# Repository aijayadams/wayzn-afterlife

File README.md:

# wayzn-afterlife

**Your Wayzn dog door doesn't have to die with the cloud, and it can come back better.**

Wayzn is shutting its service down in March 2027. The door on your slider is still a
good machine: a strong motor, a careful motor controller and a thermal sensor that sees
your dog. Only its "brain" was tied to the cloud. Swap that brain for a small ESP32
board and the door keeps working, entirely on your own network.

![Three stages. Original: the Wayzn app, Wayzn's cloud and the Electric Imp cloud drive the imp module, which drives Wayzn's STM32 motor controller and DRV8828 motor driver. Phase A, working today: your home automation talks over local Wi-Fi to an ESP32 brain that replaces the imp; Wayzn's STM32 and driver stay. Phase B, in design: one ESP32-C5 on our own board does the brain and the motor control, with a DRV8876 driver; the STM32 is gone. The door's motor, encoder, thermal sensor and case are kept throughout.](docs/before-after.svg)

## Two phases

| | What it is | Status |
|---|---|---|
| **[Phase A](#phase-a-an-esp32-brain-on-your-existing-board)** | Add an ESP32 dev board to the door's existing control board. It takes over from the cloud brain and controls the original hardware. | **Works today.** Running in a real door every day. |
| **[Phase B](#phase-b-a-replacement-control-board-in-design)** | A new control board that replaces Wayzn's entirely: same size, same connectors, an ESP32 that drives the motor itself. | **In design and validation.** Not ready to build yet. |

If you have a Wayzn door and want it working after the shutdown, **Phase A is the one to
do.**

## Phase A: an ESP32 brain on your existing board

### What you get

- **A door that keeps working.** No account, no cloud, no company that can switch it
  off.
- **Local control.** A small HTTP API on your network: open, close, live status (open,
  closed, opening, closing) and the door's settings, such as auto-open, how far it
  opens, how long it holds and how sensitive it is. A Home Assistant integration that
  uses it is available (pictured below).
- **Smarter dog detection.** The brain sees every raw reading from the door's thermal
  sensor, so it can do much better than a grid of cells and a small/medium/large
  setting. Fewer false opens, and a door that doesn't close on a dog standing beside it.
- **Safety first.** The original motor-control and current-limit (strength) firmware
  keeps running, untouched, so the door only ever pushes as hard as Wayzn designed it
  to. The door never closes on something it can see, and anything unexpected leaves it
  **open**: a dog is never locked out.
- **All open.** Firmware, wiring, measurements and the door's protocol are documented
  here, so you can fix and improve your own door.

### How it sees your dog

A tiny 8×8 thermal camera watches the doorway ten times a second. The brain keeps two
judgements apart: **presence** (a dog wants out, so open) and **occupied** (something is
in the doorway, so never close, and reverse if closing). Occupied is deliberately the
more sensitive one: a false alarm only keeps the door open a little longer. A new
detector that learns each pixel's own noise is already running alongside the current one
and catches dogs at the edge of the view that the original approach misses
([the numbers](docs/DETECTION-RESEARCH.md)).

### What it takes

If you're comfortable soldering a few wires to small pads, this is an evening's project.

1. **Open the door's case.** The shell is friction fit: no tools needed.
2. **Add an ESP32 and eight connections.** Seven wires and one jumper, all to test
   points and pads that Wayzn conveniently left on the board:

3. **Flash the firmware.** It's in [firmware/brain](firmware/brain/) (PlatformIO);
   updates after that go over Wi-Fi. The door then answers on its
   [local API](docs/API.md). For Home Assistant, the `wayzn` integration's local mode
   ([aijayadams/wayzn](https://github.com/aijayadams/wayzn)) talks to it.

## Phase B: a replacement control board (in design)

Phase A keeps Wayzn's original board and its motor controller. Phase B replaces that
board outright with an open design, so a door can be repaired or rebuilt without any
Wayzn parts, and so the motor control is open too.

#### The architecture

Wayzn's board splits the work between two chips: a cloud-connected Electric Imp module
makes the decisions, and an STM32 microcontroller runs the motor. Phase A swaps out
only the decision-maker. Phase B collapses everything into one ESP32 that both decides
and drives:

```mermaid
flowchart LR
  subgraph W["Wayzn's board (Phase A keeps it)"]
    direction TB
    IMP["Electric Imp<br/>cloud brain<br/>(Phase A: our ESP32)"] -- serial --> STM["STM32<br/>motor controller"]
    STM --> DRV1["DRV8828<br/>motor driver"]
  end
  subgraph B["Phase B board"]
    direction TB
    C5["ESP32-C5<br/>brain + motor control"] --> DRV2["DRV8876<br/>motor driver"]
    C5 -.- H2["ESP32-H2<br/>Thread, later"]
  end
```

- **One chip decides and drives.** The ESP32-C5 runs the door logic, the Wi-Fi API and
  the motor control loop. There is no second microcontroller and no serial link to keep
  in sync, and every part of the motor control is open code.
- **Hardware does the time-critical work.** The C5's built-in peripherals count every
  encoder pulse, generate the motor PWM, sample the motor current and react to a driver
  fault, all without the CPU. So Wi-Fi traffic can't make the motor miss a beat. The
  software only runs a slow outer loop: Wayzn's own controller ran at 10 ms.
- **Safety sits in silicon, not in code.** The motor driver caps the force on its own,
  at 1.1 A, matching Wayzn's limit. The motor's enable lines are held off by
  resistors, so a reset, crash or firmware update leaves the motor stopped. On top of
  that the firmware adds obstruction detection: it learns what a normal move draws and
  reverses toward open on anything more.
- **A drop-in fit.** The same outline, post holes and connector positions as Wayzn's
  board, measured from scans, so the door's cables, the case and the button cap fit
  unchanged. Below, the new board's parts are drawn over a scan of Wayzn's board: the
  red circles are the case's posts and the connector and button pins, all landing on
  Wayzn's own holes.

- **Room to grow.** An ESP32-H2 sits beside the C5 for Thread/Matter later, and an RGB
  LED under the door's light pipe gives the status more than one colour.

**Status:** the board is designed and has had an independent design review, and the
first prototypes are being ordered. It **hasn't been built or tested yet**, and the
firmware that drives the motor directly hasn't been written. Unless you want to help
validate it, use Phase A for now. Design notes: [docs/CONTROL-BOARD.md](docs/CONTROL-BOARD.md);
the KiCad project: [hardware/control-board](hardware/control-board/).

## Go deeper

| | |
|---|---|
| [How it works](docs/HOW-IT-WORKS.md) | Phase A: the board, its buses, what the motor controller does on its own, and how the brain is built |
| [Wiring](docs/HOW-IT-WORKS.md#wiring-the-esp32) | Phase A: the connection table behind the diagram above |
| [API](docs/API.md) | The brain's local HTTP API and every setting |
| [Detection research](docs/DETECTION-RESEARCH.md) | Thermal sensor measurements and the detector comparison |
| [Lab log](docs/LOG.md) · [plan](docs/PLAN.md) · [probing](docs/PROBING.md) | The research notebook: every session, the original plan and its decisions, and the probing procedures |
| [Original detection study](docs/research/2026-11-21-detection-study.md) · [captures](captures/) | The full Grid-EYE study with figures, and the raw UART/I2C logs the docs cite |
| [STM32 firmware](docs/STM-FIRMWARE.md) · [protocol](docs/STM-PROTOCOL.md) | Wayzn's motor controller: commands, states, status lines, and the motor driver's scales |
| [Hardware](docs/hardware/) | The Wayzn main board, its measured geometry, the STM32 pin map and the sensor board |
| [Control board](docs/CONTROL-BOARD.md) | Phase B: the replacement board's design, safety and control approach |
| [AGENTS.md](AGENTS.md) | The principles every change follows |

Wayzn's own STM32 firmware isn't published here; [tools/swd-dump](tools/swd-dump/) reads
your board's copy if you want one.

## What's where

| Path | Phase | What |
|---|---|---|
| `firmware/brain/` | A | The ESP32 brain firmware (PlatformIO) |
| `tools/` | A | The probing tools used to understand the board (UART/I2C sniffers, SWD dump, power test, Ghidra scripts) |
| `docs/` | A, B | How it works, the API, the door's protocol, measurements, and the Phase B design notes |
| `hardware/control-board/` | B | The replacement control board: KiCad project generated from Python, fab and order files |
| `hardware/carrier/` | A (parked) | A plug-in carrier PCB for the Phase A brain. Not needed (the dev-board wiring works); kept for reference |
| `photos/` | | Board photos and scans (serial labels blurred, no location data) |

## Join in

Own a Wayzn door? [Open an issue](https://github.com/aijayadams/wayzn-afterlife/issues)
with questions, your board's revision, photos, or ideas. Every door that keeps running
is a win.

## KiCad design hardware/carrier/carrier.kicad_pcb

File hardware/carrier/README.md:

# Phase A carrier board v3 (WYP-BC-100 piggyback, parked)

A 4-layer board (53.8 x 33.4 mm) that replaces the hand-wired ESP32 DevKit. It sits parallel to the Wayzn
WYP-BC-100, above the STM32 end, inside one ~57 mm cell between the lid ribs. It plugs in: no screws, no
spacers, no soldering to test points.

Status: **laid out by hand and checked (ERC, DRC with schematic parity, courtyards, silkscreen: all clean); not
ordered.** The Wayzn-side positions come from the photos plus caliper readings, so check the 1:1 print before
ordering (see "Before ordering").

Pictures: `out/overlay-top.jpg` (the carrier and the lid ribs drawn on the Wayzn board photo), `out/render-top.png`,
`out/render-bottom.png`, `out/plan.png` (pads, nets and routes on a 1 mm grid).

## How it sits

- **x**: from 1 mm inside the lid rib beyond J105 (x -30) to 2 mm short of the rib that runs through the end
  posts (x 23.8). The Wayzn J2/J5 sockets (6.6 mm tall) stay uncovered past the carrier's end, so their cables
  plug in as before.
- **y**: within the Wayzn board's 34 mm width. Its top edge already touches the shell, so the carrier doesn't go
  past it.
- **Held by two connectors on its underside**:
  - **J1**: a round-hole 1x4 socket onto a round-pin 1x4 header soldered into the STM+IMP holes (standard square
    pins don't fit them). It carries 3V3, the STM UART and GND.
  - **J6**: a 2x4 2.0 mm male header plugged into the Wayzn **J105** socket. Mechanical only: every pin is
    unconnected on the carrier.
- **Stack height**: J105 plus J6's plastic sets the gap; the J1 socket and header heights have to match it.
  **J105's height still needs measuring** (`STACK_MM` in design.py is a placeholder 11 mm).

## What's on it

| Part | Why |
|---|---|
| **ESP32-C5-WROOM-1U-N8R8** (U1) | Main MCU: dual-band Wi-Fi 6 (2.4 + 5 GHz), BLE 5, 802.15.4; 8 MB flash + 8 MB PSRAM. U.FL (MHF I) antenna socket on the module: use a **2.4/5 GHz** antenna |
| **ESP32-H2-MINI-1U-H4S** (U2) | Thread/Zigbee radio, OpenThread RCP on UART; the C5 resets and reflashes it (EN, GPIO9). **W.FL / MHF III ("IPEX3")** antenna socket: 2.4 GHz antennas with that plug are sold as IPEX3/MHF3 (e.g. AliExpress, Ditronix, Adafruit 5445). Espressif certified it with an antenna of at most 2.33 dBi |
| **LIS2DH12** (U3) | Accelerometer for the drive-lever pose (the Wayzn board's KXTJ3 stopped answering). I2C 0x19 (SA0 open, on its internal pull-up; firmware must not disable it) |
| J1 1x4 round-hole socket (underside) | Onto a round-pin header in the Wayzn **STM+IMP** holes: 3V3, STM TX, STM RX, GND |
| J6 2x4 2.0 mm header (underside) | Into the Wayzn J105: second anchor, mechanical only |
| J2 / J3 JST PH 4-pin, top entry | I2C pass-through. The Grid-EYE cable moves from the Wayzn J2 to J3. A straight PH-PH cable runs from J2 to the Wayzn J2 (same pin order: GND, SCL, SDA, 3V3). Brings the bus and the Wayzn board's 4.7k pull-ups |
| J4 JST PH 2-pin | STM32 NRST: one wire from SW300's top-right pad (the only hand-soldered joint on the Wayzn board, as today) |
| **J5 1x6 2.54 mm, RESET and BOOT buttons** | Programming, see below |
| JP1 (solder jumper, open) | Connects J5 pin 1 to 3V3 for a bench flash only |
| D1 | Status LED (GPIO3) |

## Programming (first flash; OTA after that)

J5, top to bottom (printed beside each pin): **3V3\*, GND, EN, TXO, RXI, BOOT**. Any 3.3 V USB-serial adapter:
adapter GND to GND, adapter RX to TXO, adapter TX to RXI. Either let esptool drive EN/BOOT through DTR/RTS, or
by hand: hold **BOOT**, tap **RESET**, release BOOT, flash.

- **On the door** (normal): the door powers the board. Leave the adapter's 3V3 unconnected; JP1 stays open, so
  J5 pin 1 isn't connected to anything.
- **On the bench** (board off the door): bridge JP1 with solder, power the board from the adapter's 3V3 on J5
  pin 1. Remove the bridge before fitting it to the door, so the adapter and the door's rail can never meet.
- The H2 needs no programming access of its own: the C5 holds its BOOT strap low, resets it and flashes it over
  their UART (esp-serial-flasher), like Espressif's Thread Border Router board.

## Power

All from the Wayzn 3V3 rail (J1 and J2). The old ESP32 ran from it at full Wi-Fi load with no brownouts
(measured on the door, 2026-11-21); the C5 datasheet asks for a 600 mA supply (H2: 350 mA), so **check the rail under C5 +
H2 load**. Bulk 22 uF at entry, 22 uF + 100 nF at the C5, 10 uF + 100 nF at the H2. EN delays 10k/1u on both
chips; the firmware should also wait ~1 s before starting Wi-Fi.

## Pin map (C5)

| GPIO (module pin) | Net | Notes |
|---|---|---|
| EN (3) | C5_EN | 10k/1u, RESET button, J5 |
| 2 (4) | STM_NRST | open-drain, 100 R, J4 |
| 3 (5) | LED_STATUS | 1k. Strap MTDI: SDIO timing only, unused here |
| 9 (11) | H2_BOOT | open-drain to H2 GPIO9 (10k pull-up) |
| 10 (12) | H2_EN | open-drain to H2 EN (10k/1u) |
| 28 (15) | C5_BOOT | strap: 10k pull-up, BOOT button, J5 |
| 5 (16) / 4 (17) | H2_TXD / H2_RXD | from H2 U0TXD (GPIO24) / to H2 U0RXD (GPIO23) |
| 27 (18) | ACC_INT1 | strap: LIS2DH12 INT1 idles low, which only selects UART-download variant 1 over 0 |
| 23 (21) / 24 (23) | I2C_SCL / I2C_SDA | Grid-EYE 0x69, LIS2DH12 0x19, (dead KXTJ3 0x0F) |
| 12 (24) / 11 (25) | C5_RXD0 / C5_TXD0 | J5 |
| 25 (26) | STM_TX | UART1 RX from STM32 PA9, 100 R. Strap: SDIO timing only |
| 26 (27) | STM_RX | UART1 TX to STM32 PA10, 100 R |
| 0, 1, 6, 7, 8, 13, 14 | unused | module pin 19 (PSRAM chip select) must stay unconnected |

H2: GPIO8 10k pull-up (download mode needs it high); VBAT tied to 3V3.

## Layout

Placement, every signal route, and every silkscreen label are written out in `layout.py` (coordinates in the
Wayzn board's frame, so the carrier lines up with the board under it). Floorplan: programming zone on the left
(J5 on the edge, RESET above BOOT, the bench-3V3 jumper, J6 underneath); the C5 in the middle (left-edge pins
toward the programming zone, right-edge pins toward J1, the I2C parts and the H2); along the top edge, the status
LED, J4 (NRST) and J2; J3 on the right end; the accelerometer between J1 and J3; the H2 in the bottom-right
corner, rotated 180 so its UART faces the C5. Pins were chosen so no two signals cross. Each power pad gets its
own via to the In1 (GND) / In2 (3V3) plane. The LIS2DH12 (0.5 mm pitch) is wired to its decoupling caps instead.
GND stitching vias on a 3 mm grid.

Stackup: F.Cu signals + GND pour, In1 GND, In2 3V3, B.Cu signals + GND pour. 0.12 mm clearance (the LIS2DH12's
pads leave exactly 0.15 mm), 0.2 mm signal / 0.3 mm power tracks, 0.6/0.3 mm vias (JLC 4-layer minimum 0.09 mm).

Silkscreen: only the labels in `layout.SILK`: J5's pin names (one beside each pin), RESET/BOOT, the jumper, the
connectors, and a short how-to on the back. Footprint silk that would leave the board or run into a label is
dropped. Part values aren't drawn, and references stay on the assembly layer. The build fails if a label leaves
the board or touches a pad, via or another label.

**Don't edit `carrier.kicad_pcb` in KiCad and expect it to stick: `build.sh` regenerates it from `layout.py`.**
Change `layout.py` (or `design.py`) and rebuild.

## Files

- `design.py`: parts, nets, LCSC numbers, mechanics, rules. `layout.py`: placement, routes, silkscreen.
- `build.sh`: regenerates everything: `mk_carrier_sym.py` → `lib/Carrier.kicad_sym`; `gen_sch.py` →
  `carrier.kicad_sch`; `gen_pcb.py` (+ `route.py` for fanout and stitching) → `carrier.kicad_pcb`; ERC; DRC with
  schematic parity; `fab.py` → `fab/`. Needs KiCad 10.
- `fab/`: `carrier-gerbers.zip`, `carrier-bom.csv`, `carrier-cpl.csv` (JLC formats).
- `padmap.py`, `planplot.py`: pad coordinates and `out/plan.png`, for working on routes. `overlay.py` →
  `out/overlay-top.jpg`. `out/fit-check-1to1.pdf`: print at 100 % and lay it on the real board.
- `lib/Espressif.*`: vendored from espressif/kicad-libraries (CC-BY-SA 4.0 with the KiCad design exception).

## BOM and sourcing (checked 2026-11-23/24, mostly from search snapshots: confirm live before ordering)

| Ref | Part | LCSC | Notes |
|---|---|---|---|
| U1 | ESP32-C5-WROOM-1U-N8R8 | C51950748 | LCSC 0 (live read). Buy from Mouser |
| U2 | ESP32-H2-MINI-1U-H4S | C49450282 | DigiKey/Mouser hundreds. (The -H4 is not recommended for new designs) |
| U3 | LIS2DH12TR | C110926 | Patchy stock. Optional: the board works without it |
| SW1, SW2 | XKB TS-1187A-B-A-B | C318884 | JLC Basic |
| D1 | XL-1608UGC-04 green 0603 | C965804 | |
| J2, J3 | JST B4B-PH-K-S (4-pin PH, top entry) | C131334 | |
| J4 | JST B2B-PH-K-S | C131337 | |
| J6 | HCTL PZ200-2-04-Z, 2x4 2.0 mm straight | C2905990 | alt C225289 (check it's straight). Hand-solder on the underside |
| J1 | 1x4 2.54 round-hole (machined) socket | (C7495238?) | Mill-Max 310-43-104-41-001000 or CONNFLY C7495238. **Height to pick once J105 is measured**. Hand-solder on the underside |
| J5 | 1x6 2.54 male header | | cut from a strip; hand-solder |
| R, C | 0402/0603/0805 | C25744, C25076, C11702, C1525, C52923, C19702, C45783 | all JLC Basic |

Also: a round-pin 1x4 header for the Wayzn STM+IMP holes (Mill-Max 350-10-104-00-006000, 0.46 mm pins); a
straight 4-pin PH-PH cable, 100-150 mm (Adafruit 3568 or Pololu 5623/5624: check pin 1 to pin 1 with a meter); a
2-pin PH lead for NRST; antennas: 2.4/5 GHz U.FL (C5), 2.4 GHz MHF III (H2). Full list: `fab/order-bom.csv`.

## Before ordering

0. **Strapping fix needed (found 2026-11-24 on the control board):** UART download needs GPIO27 high when BOOT
   holds GPIO28 low, but here GPIO27 is the accelerometer's INT1, which idles low. Move a pulled-up signal
   (e.g. I2C SDA) onto GPIO27 before ordering, as hardware/control does.

1. **Measure J105's height** above the Wayzn board. It sets the stack, so pick the J1 socket and round-pin header
   heights to match, and check the stack clears everything underneath (U300, SW300, the imp module's edge).
2. Print `out/fit-check-1to1.pdf` at 100 % and lay it on the board: J1 over the STM+IMP holes, J6 over J105, both
   ends inside the lid ribs. The Wayzn landmarks are drawn on it.
3. Check the Grid-EYE cable reaches J3; if not, add a PH extension.
4. Firmware: port to the C5 (Arduino-ESP32 3.x / pioarduino; single core), pin map above, H2 RCP flashing.

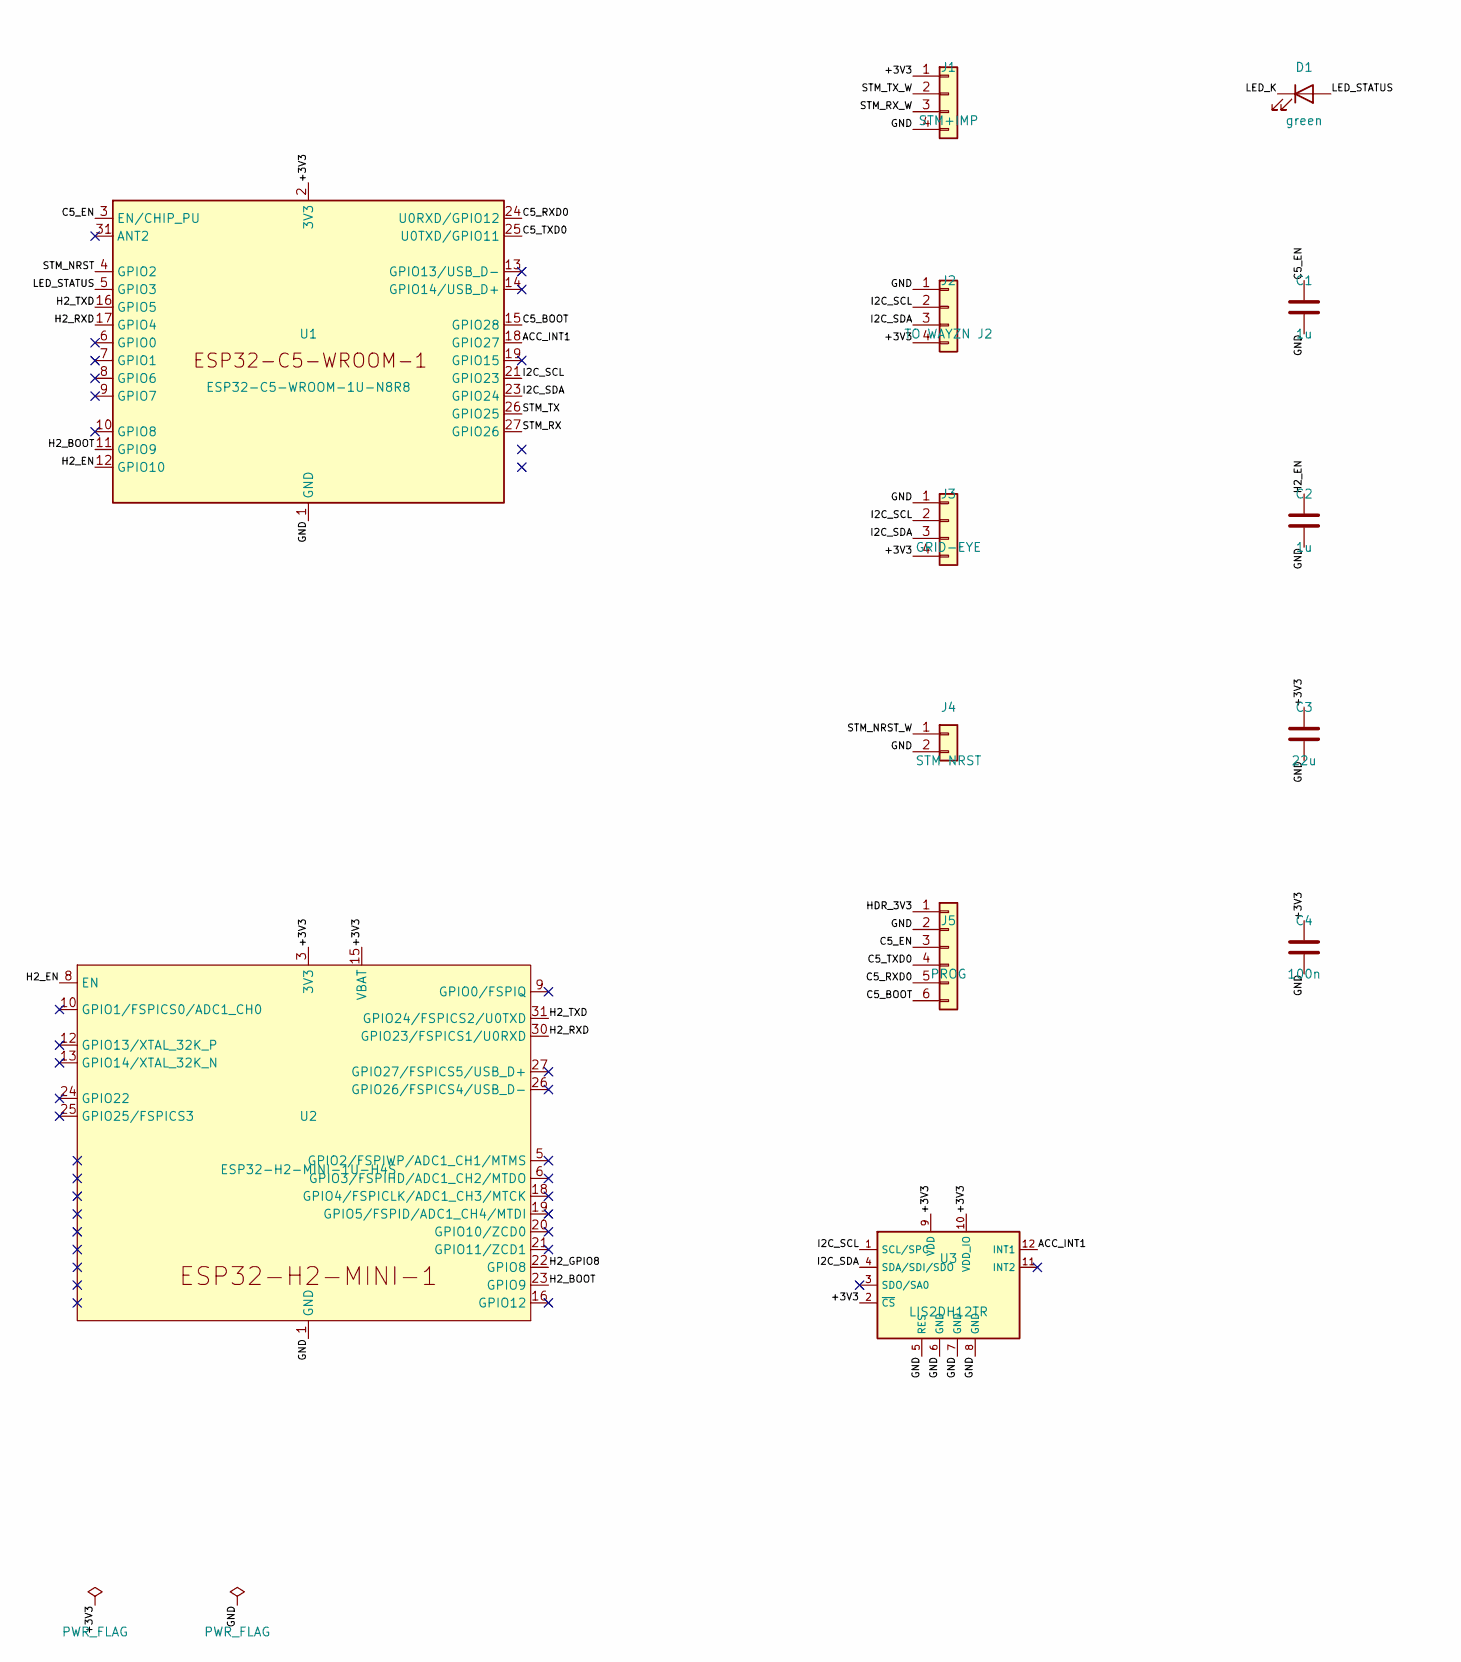
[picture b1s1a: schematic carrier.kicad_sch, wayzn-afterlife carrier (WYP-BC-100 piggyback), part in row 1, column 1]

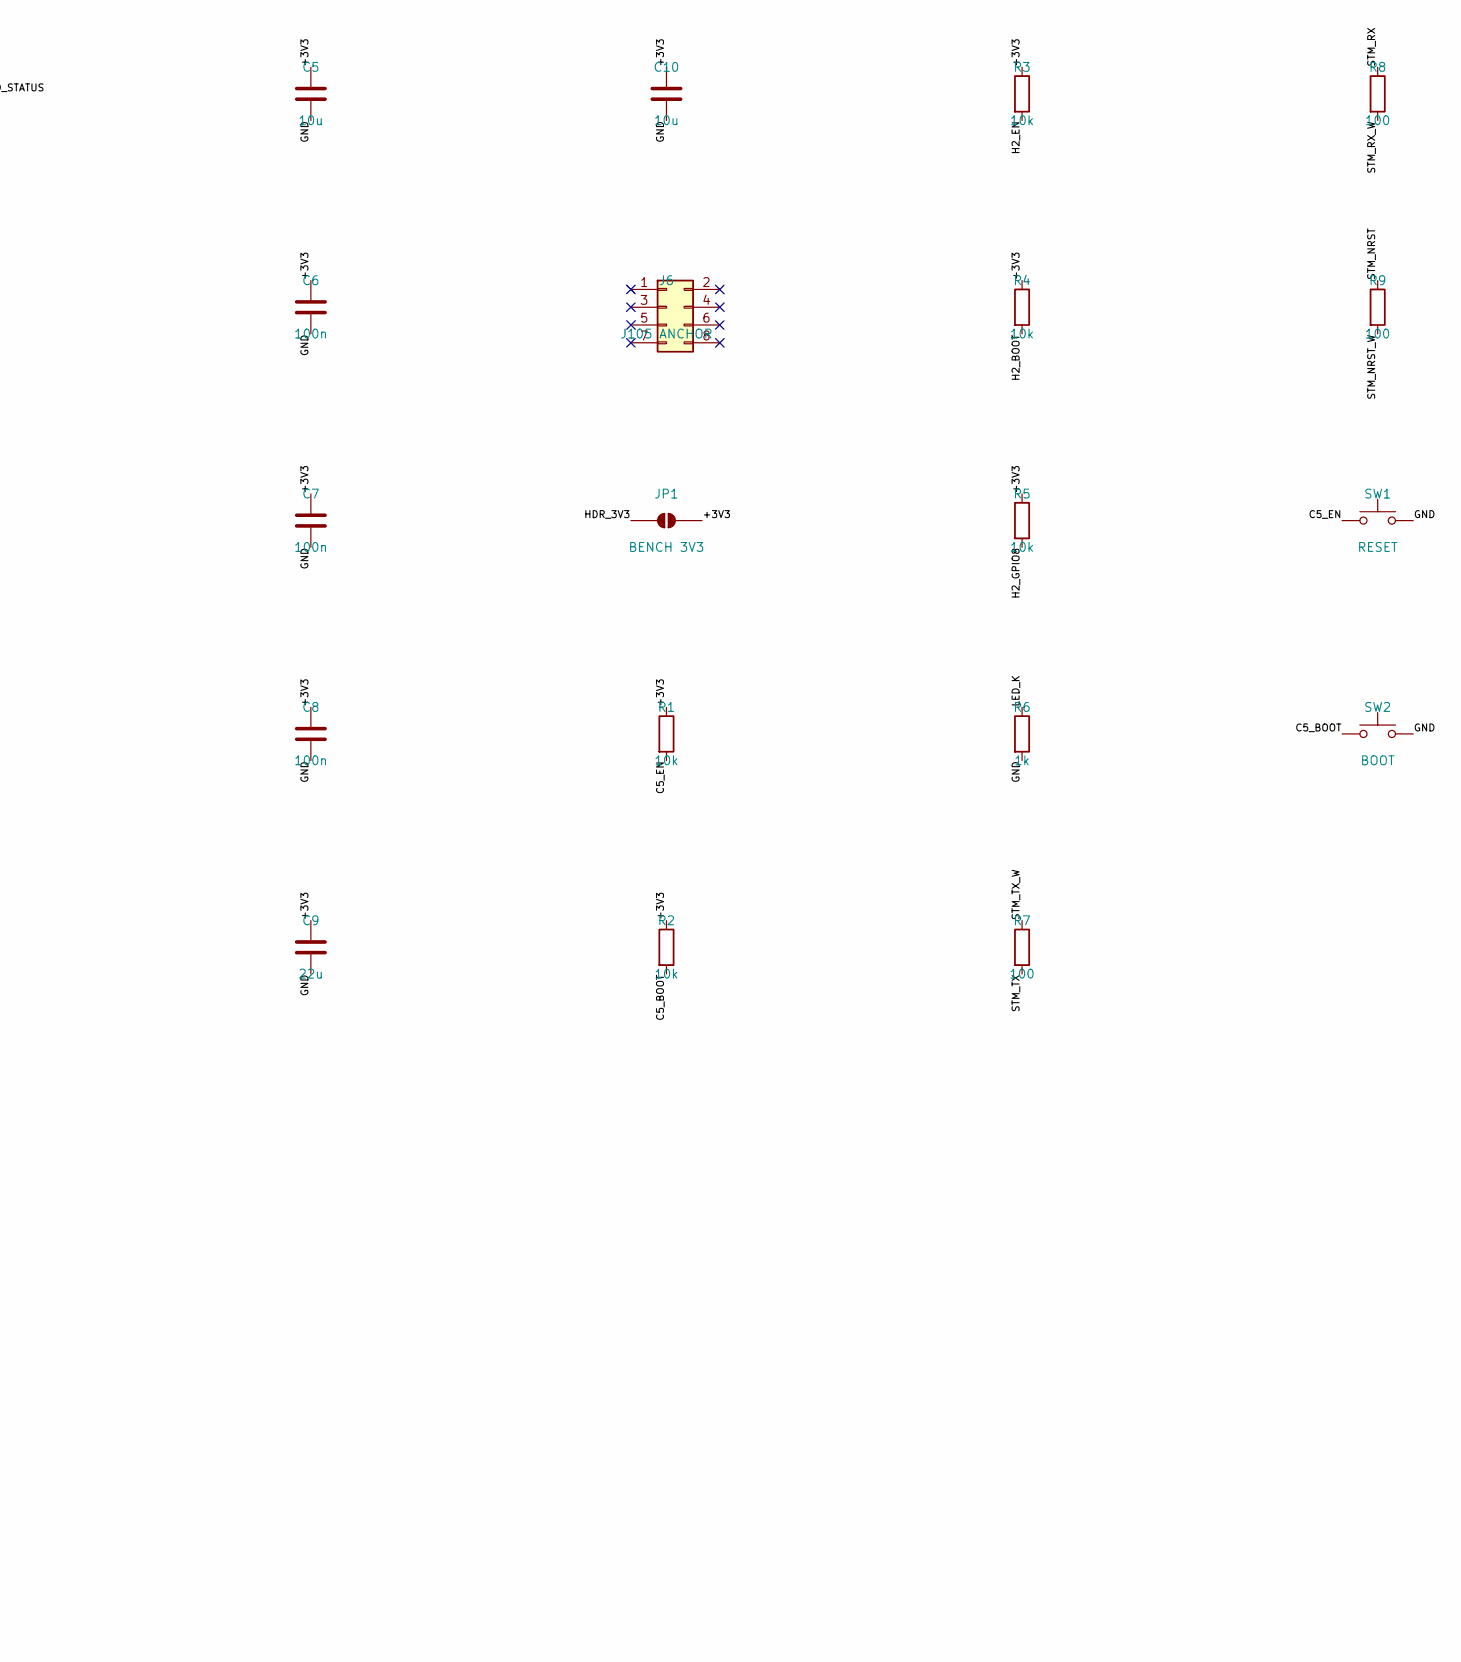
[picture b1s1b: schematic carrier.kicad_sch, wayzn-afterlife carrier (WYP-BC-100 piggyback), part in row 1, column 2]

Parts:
C1, C2: 1u; C_0402_1005Metric; LCSC C52923
C3, C9: 22u; C_0805_2012Metric; LCSC C45783
C4, C6, C7, C8: 100n; C_0402_1005Metric; LCSC C1525
C5, C10: 10u; C_0603_1608Metric; LCSC C19702
D1: green; LED_0603_1608Metric; LCSC C965804
J1: STM+IMP; PinSocket_1x04_P2.54mm_Vertical
J2: TO WAYZN J2; JST_PH_B4B-PH-K_1x04_P2.00mm_Vertical; LCSC C131334
J3: GRID-EYE; JST_PH_B4B-PH-K_1x04_P2.00mm_Vertical; LCSC C131334
J4: STM NRST; JST_PH_B2B-PH-K_1x02_P2.00mm_Vertical; LCSC C131337
J5: PROG; PinHeader_1x06_P2.54mm_Vertical
J6: J105 ANCHOR; PinHeader_2x04_P2.00mm_Vertical; LCSC C2905990
JP1: BENCH 3V3; SolderJumper-2_P1.3mm_Open_RoundedPad1.0x1.5mm
R1, R2, R3, R4, R5: 10k; R_0402_1005Metric; LCSC C25744
R6: 1k; R_0402_1005Metric; LCSC C11702
R7, R8, R9: 100; R_0402_1005Metric; LCSC C25076
SW1: RESET; SW_Push_1P1T_XKB_TS-1187A; LCSC C318884
SW2: BOOT; SW_Push_1P1T_XKB_TS-1187A; LCSC C318884
U1: ESP32-C5-WROOM-1U-N8R8; ESP32-C5-WROOM-1U; LCSC C51950748
U2: ESP32-H2-MINI-1U-H4S; ESP32-H2-MINI-1U; LCSC C49450282
U3: LIS2DH12TR; LGA-12_2x2mm_P0.5mm; LCSC C110926

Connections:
/+3V3: C3.1, C4.1, C5.1, C6.1, C7.1, C8.1, C9.1, C10.1, J1.1, J2.4, J3.4, JP1.2 (B), R1.1, R2.1, R3.1, R4.1, R5.1, U1.2 (3V3), U2.3 (3V3), U2.15 (VBAT), U3.2 (~CS), U3.9 (VDD), U3.10 (VDD_IO)
/ACC_INT1: U1.18 (GPIO27), U3.12 (INT1)
/C5_BOOT: J5.6, R2.2, SW2.1, U1.15 (GPIO28)
/C5_EN: C1.1, J5.3, R1.2, SW1.1, U1.3 (EN/CHIP_PU)
/C5_RXD0: J5.5, U1.24 (U0RXD/GPIO12)
/C5_TXD0: J5.4, U1.25 (U0TXD/GPIO11)
/GND: C1.2, C2.2, C3.2, C4.2, C5.2, C6.2, C7.2, C8.2, C9.2, C10.2, J1.4, J2.1, J3.1, J4.2, J5.2, R6.2, SW1.2, SW2.2, U1.1 (GND), U1.28 (GND), U1.29 (GND), U1.30 (GND), U1.32 (GND), U2.1 (GND), U2.2 (GND), U2.11 (GND), U2.14 (GND), U2.36 (GND), U2.37 (GND), U2.38 (GND), U2.39 (GND), U2.40 (GND), U2.41 (GND), U2.42 (GND), U2.43 (GND), U2.44 (GND), U2.45 (GND), U2.46 (GND), U2.47 (GND), U2.48 (GND), U2.49 (GND), U2.50 (GND), U2.51 (GND), U2.52 (GND), U2.53 (GND), U3.5 (RES), U3.6 (GND), U3.7 (GND), U3.8 (GND)
/H2_BOOT: R4.2, U1.11 (GPIO9), U2.23 (GPIO9)
/H2_EN: C2.1, R3.2, U1.12 (GPIO10), U2.8 (EN)
/H2_GPIO8: R5.2, U2.22 (GPIO8)
/H2_RXD: U1.17 (GPIO4), U2.30 (GPIO23/FSPICS1/U0RXD)
/H2_TXD: U1.16 (GPIO5), U2.31 (GPIO24/FSPICS2/U0TXD)
/HDR_3V3: J5.1, JP1.1 (A)
/I2C_SCL: J2.2, J3.2, U1.21 (GPIO23), U3.1 (SCL/SPC)
/I2C_SDA: J2.3, J3.3, U1.23 (GPIO24), U3.4 (SDA/SDI/SDO)
/LED_K: D1.1 (K), R6.1
/LED_STATUS: D1.2 (A), U1.5 (GPIO3)
/STM_NRST: R9.1, U1.4 (GPIO2)
/STM_NRST_W: J4.1, R9.2
/STM_RX: R8.1, U1.27 (GPIO26)
/STM_RX_W: J1.3, R8.2
/STM_TX: R7.2, U1.26 (GPIO25)
/STM_TX_W: J1.2, R7.1

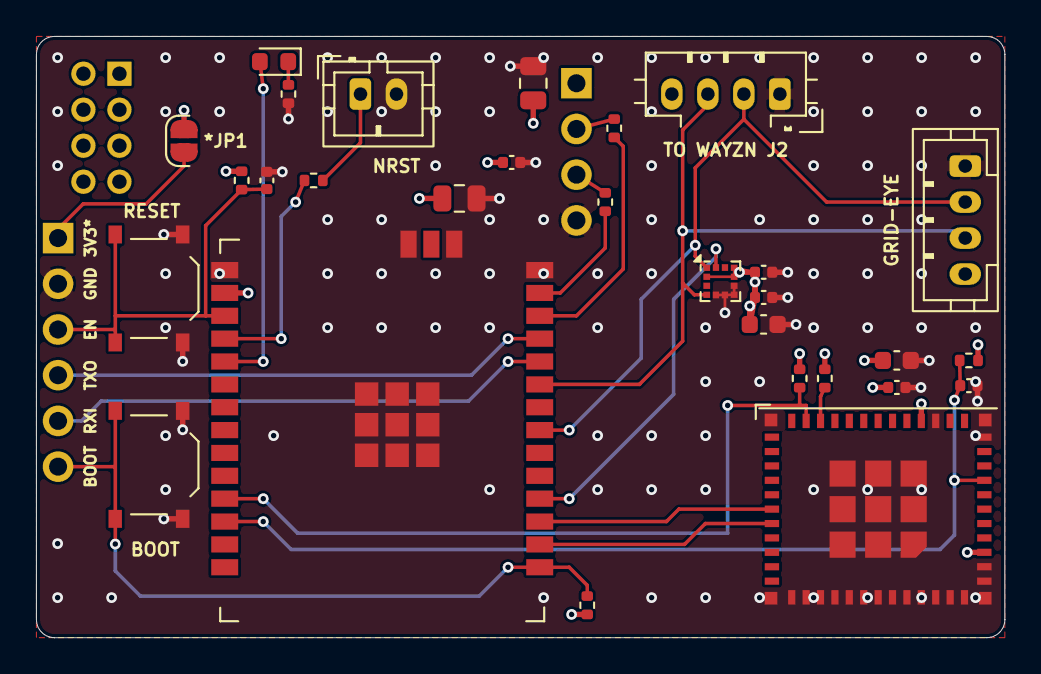
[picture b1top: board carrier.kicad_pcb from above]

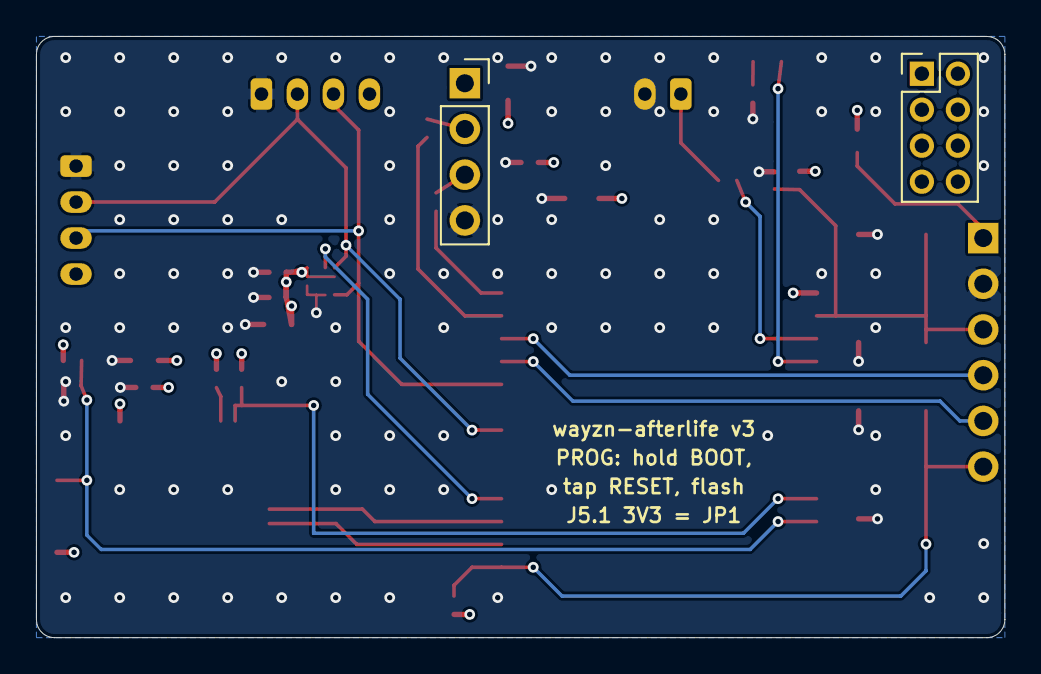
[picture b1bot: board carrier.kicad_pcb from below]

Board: 4 copper layers, 53.8 x 33.4 mm, 32 parts (2 on the bottom side), 23 nets.

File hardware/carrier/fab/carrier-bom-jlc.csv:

Comment,Designator,Footprint,LCSC
1u,"C1,C2",C_0402_1005Metric,C52923
22u,"C3,C9",C_0805_2012Metric,C45783
100n,"C4,C6,C7,C8",C_0402_1005Metric,C1525
10u,"C5,C10",C_0603_1608Metric,C19702
10k,"R1,R2,R3,R4,R5",R_0402_1005Metric,C25744
1k,R6,R_0402_1005Metric,C11702
100,"R7,R8,R9",R_0402_1005Metric,C25076
RESET,SW1,SW_Push_1P1T_XKB_TS-1187A,C318884
BOOT,SW2,SW_Push_1P1T_XKB_TS-1187A,C318884
LIS2DH12TR,U3,LGA-12_2x2mm_P0.5mm,C110926
